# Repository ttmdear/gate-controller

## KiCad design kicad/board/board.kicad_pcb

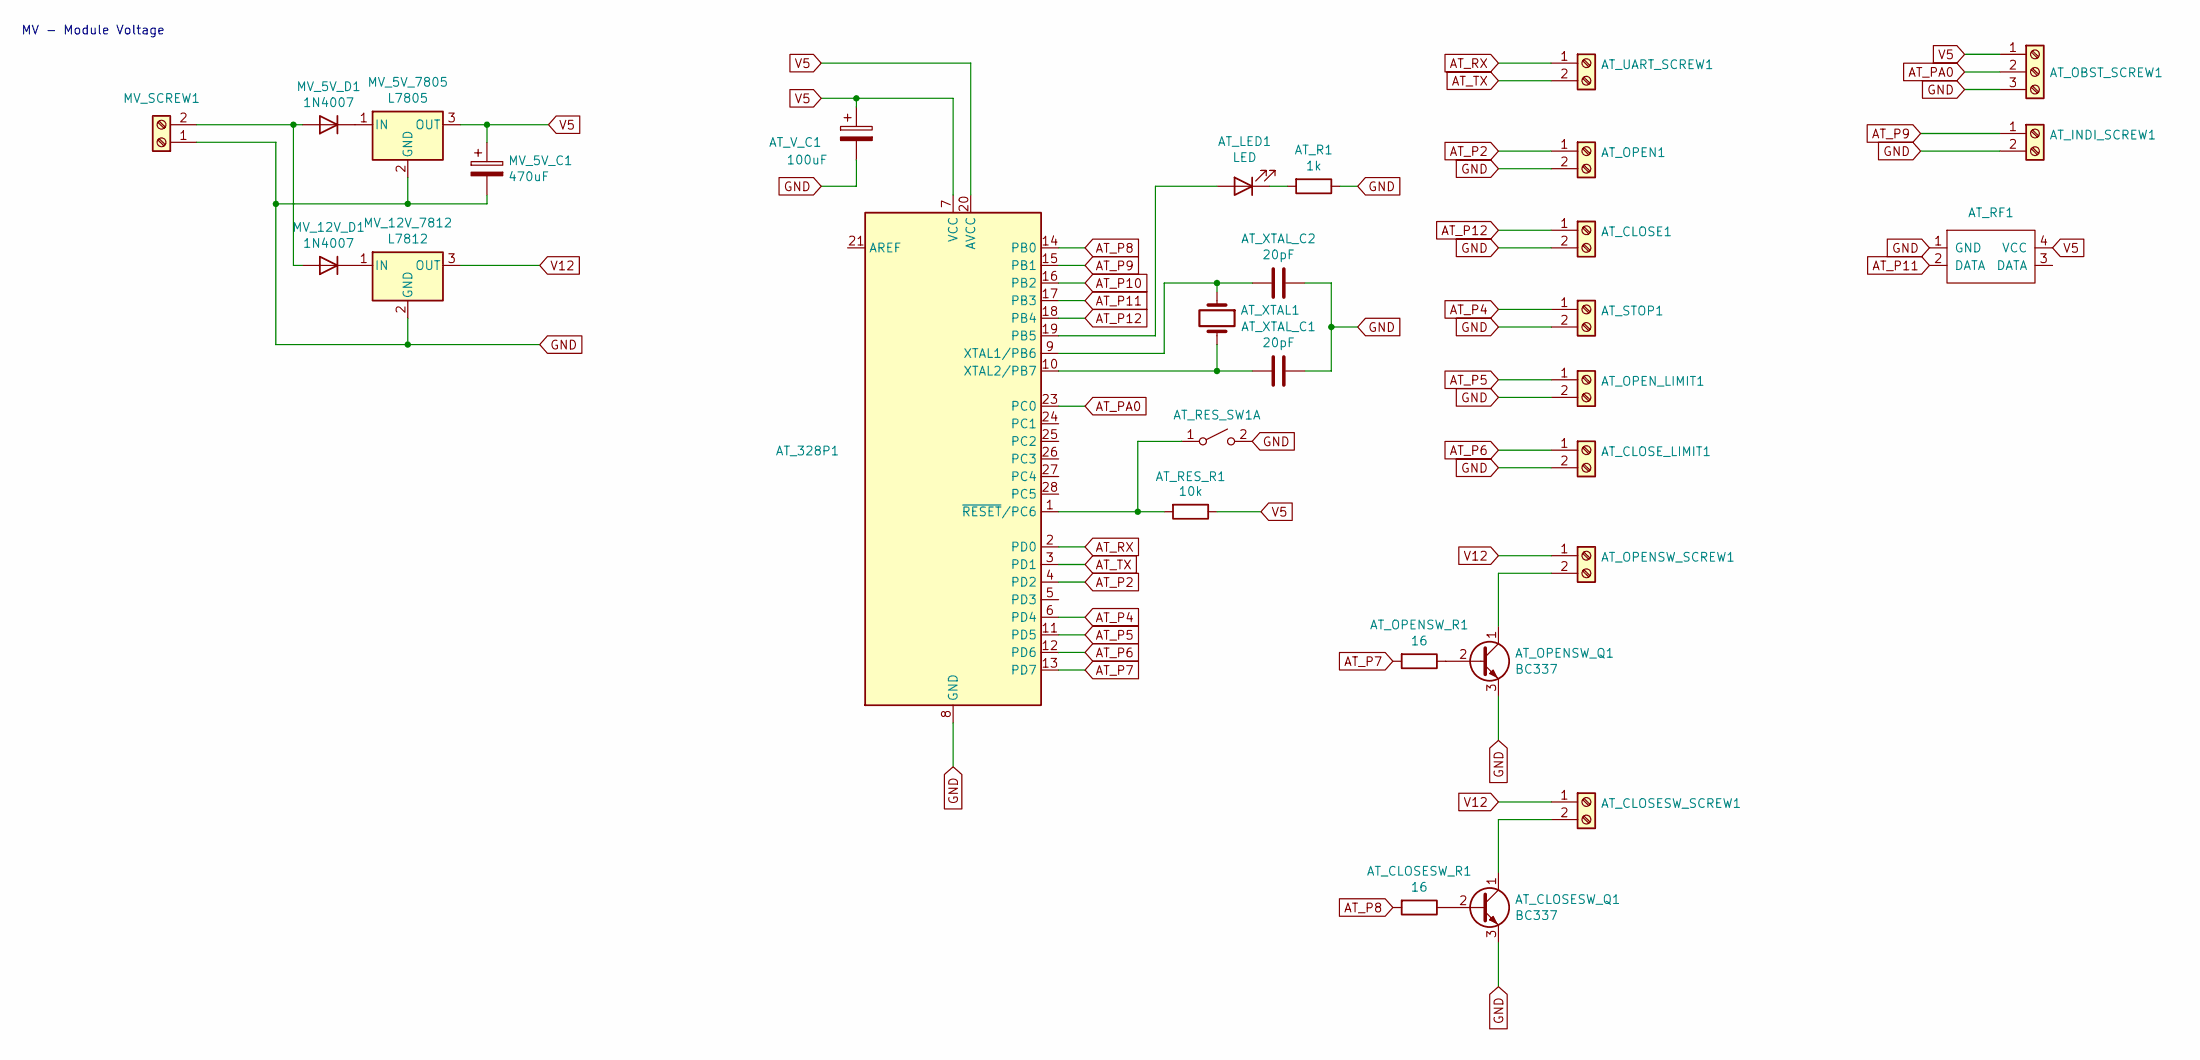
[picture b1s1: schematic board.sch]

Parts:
AT_328P1: http://www.microchip.com/filehandler/redirect?htt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; DIP-28_W7.62mm
AT_CLOSE1: Screw_Terminal_01x02; TerminalBlock_bornier-2_P5.08mm
AT_CLOSESW_Q1: BC337; TO-92
AT_CLOSESW_R1: 16; R_Axial_DIN0204_L3.6mm_D1.6mm_P5.08mm_Horizontal
AT_CLOSESW_SCREW1: Screw_Terminal_01x02; TerminalBlock_bornier-2_P5.08mm
AT_CLOSE_LIMIT1: Screw_Terminal_01x02; TerminalBlock_bornier-2_P5.08mm
AT_INDI_SCREW1: Screw_Terminal_01x02; TerminalBlock_bornier-2_P5.08mm
AT_LED1: LED; LED_D5.0mm
AT_OBST_SCREW1: Screw_Terminal_01x03; TerminalBlock_bornier-3_P5.08mm
AT_OPEN1: Screw_Terminal_01x02; TerminalBlock_bornier-2_P5.08mm
AT_OPENSW_Q1: BC337; TO-92
AT_OPENSW_R1: 16; R_Axial_DIN0204_L3.6mm_D1.6mm_P5.08mm_Horizontal
AT_OPENSW_SCREW1: Screw_Terminal_01x02; TerminalBlock_bornier-2_P5.08mm
AT_OPEN_LIMIT1: Screw_Terminal_01x02; TerminalBlock_bornier-2_P5.08mm
AT_R1: 1k; R_Axial_DIN0204_L3.6mm_D1.6mm_P2.54mm_Vertical
AT_RES_R1: 10k; R_Axial_DIN0204_L3.6mm_D1.6mm_P5.08mm_Horizontal
AT_RES_SW1: 1; SW_PUSH_6mm
AT_RF1: RF_RX_433MHz
AT_STOP1: Screw_Terminal_01x02; TerminalBlock_bornier-2_P5.08mm
AT_UART_SCREW1: Screw_Terminal_01x02; TerminalBlock_bornier-2_P5.08mm
AT_V_C1: 100uF; CP_Radial_D8.0mm_P5.00mm
AT_XTAL1: Crystal; Resonator-2Pin_W6.0mm_H3.0mm
AT_XTAL_C1, AT_XTAL_C2: 20pF; CP_Radial_D8.0mm_P3.80mm
MV_5V_7805: L7805; TO-220-3_Vertical
MV_5V_C1: 470uF; CP_Radial_D8.0mm_P5.00mm
MV_5V_D1, MV_12V_D1: 1N4007; D_T-1_P5.08mm_Horizontal
MV_12V_7812: L7812; TO-220-3_Vertical
MV_SCREW1: 12V; TerminalBlock_bornier-2_P5.08mm

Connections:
AT_P2: AT_328P1.4 (PD2), AT_OPEN1.1
AT_P4: AT_328P1.6 (PD4), AT_STOP1.1
AT_P5: AT_328P1.11 (PD5), AT_OPEN_LIMIT1.1
AT_P6: AT_328P1.12 (PD6), AT_CLOSE_LIMIT1.1
AT_P7: AT_328P1.13 (PD7), AT_OPENSW_R1.2
AT_P8: AT_328P1.14 (PB0), AT_CLOSESW_R1.2
AT_P9: AT_328P1.15 (PB1), AT_INDI_SCREW1.1
AT_P10: AT_328P1.16 (PB2)
AT_P11: AT_328P1.17 (PB3), AT_RF1.2 (DATA)
AT_P12: AT_328P1.18 (PB4), AT_CLOSE1.1
AT_PA0: AT_328P1.23 (PC0), AT_OBST_SCREW1.2
AT_RX: AT_328P1.2 (PD0), AT_UART_SCREW1.1
AT_TX: AT_328P1.3 (PD1), AT_UART_SCREW1.2
GND: AT_328P1.8 (GND), AT_328P1.22 (GND), AT_CLOSE1.2, AT_CLOSESW_Q1.3 (E), AT_CLOSE_LIMIT1.2, AT_INDI_SCREW1.2, AT_OBST_SCREW1.3, AT_OPEN1.2, AT_OPENSW_Q1.3 (E), AT_OPEN_LIMIT1.2, AT_R1.1, AT_RES_SW1.2 (B), AT_RF1.1 (GND), AT_STOP1.2, AT_V_C1.2, AT_XTAL_C1.1, AT_XTAL_C2.1, MV_5V_7805.2 (GND), MV_5V_C1.2, MV_12V_7812.2 (GND), MV_SCREW1.1
unnamed: AT_328P1.1 (~RESET~/PC6), AT_RES_R1.2, AT_RES_SW1.1 (A)
unnamed: AT_328P1.9 (XTAL1/PB6), AT_XTAL1.1, AT_XTAL_C2.2
unnamed: AT_328P1.10 (XTAL2/PB7), AT_XTAL1.2, AT_XTAL_C1.2
unnamed: AT_328P1.19 (PB5), AT_LED1.2 (A)
unnamed: AT_CLOSESW_Q1.1 (C), AT_CLOSESW_SCREW1.2
unnamed: AT_CLOSESW_Q1.2 (B), AT_CLOSESW_R1.1
unnamed: AT_LED1.1 (K), AT_R1.2
unnamed: AT_OPENSW_Q1.1 (C), AT_OPENSW_SCREW1.2
unnamed: AT_OPENSW_Q1.2 (B), AT_OPENSW_R1.1
unnamed: MV_5V_7805.1 (IN), MV_5V_D1.1 (K)
unnamed: MV_12V_7812.1 (IN), MV_12V_D1.1 (K)
unnamed: MV_5V_D1.2 (A), MV_12V_D1.2 (A), MV_SCREW1.2
V5: AT_328P1.7 (VCC), AT_328P1.20 (AVCC), AT_OBST_SCREW1.1, AT_RES_R1.1, AT_RF1.4 (VCC), AT_V_C1.1, MV_5V_7805.3 (OUT), MV_5V_C1.1
V12: AT_CLOSESW_SCREW1.1, AT_OPENSW_SCREW1.1, MV_12V_7812.3 (OUT)

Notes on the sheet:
MV - Module Voltage

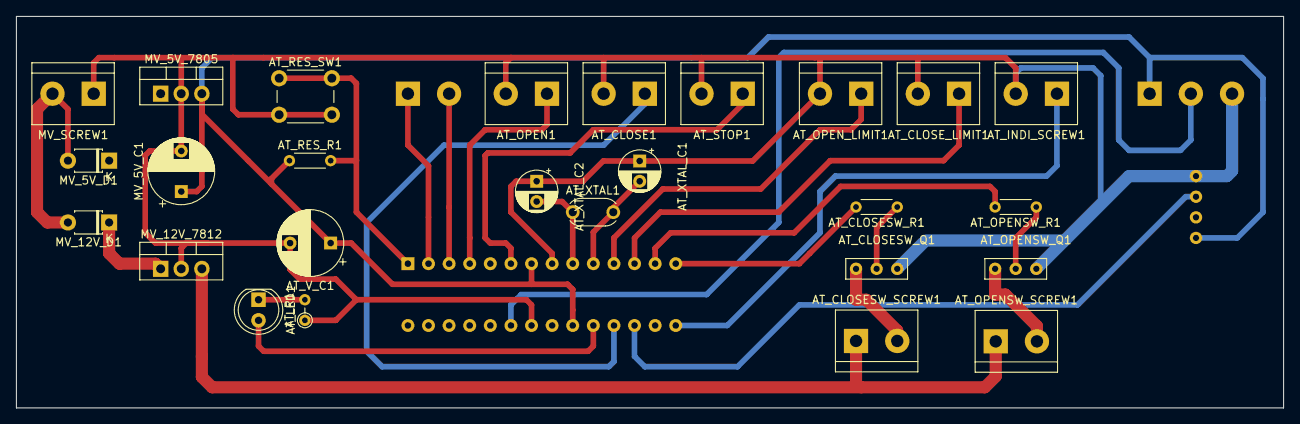
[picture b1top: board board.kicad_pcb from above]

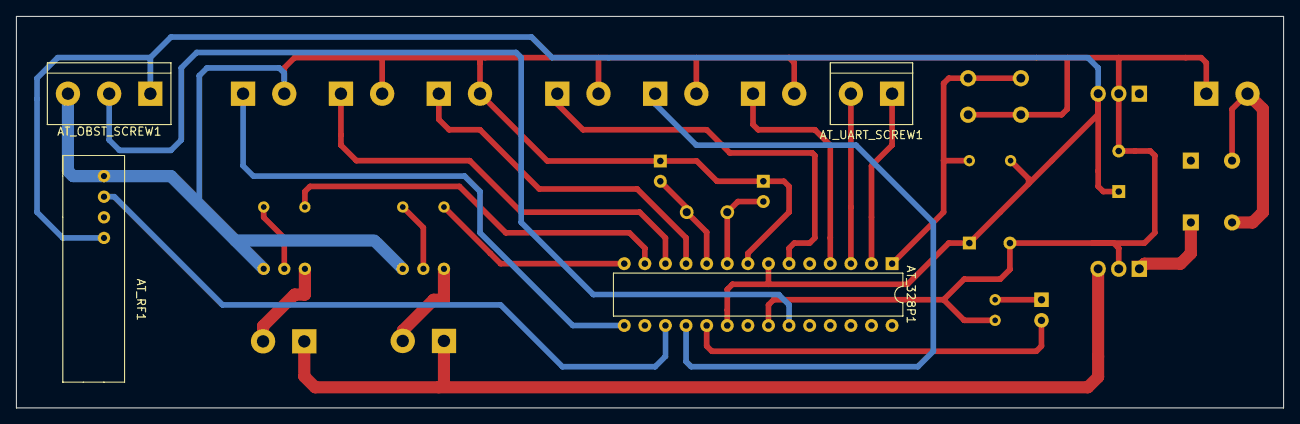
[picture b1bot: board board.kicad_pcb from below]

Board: 2 copper layers, 156.2 x 48.3 mm, 30 parts (4 on the bottom side), 27 nets.
